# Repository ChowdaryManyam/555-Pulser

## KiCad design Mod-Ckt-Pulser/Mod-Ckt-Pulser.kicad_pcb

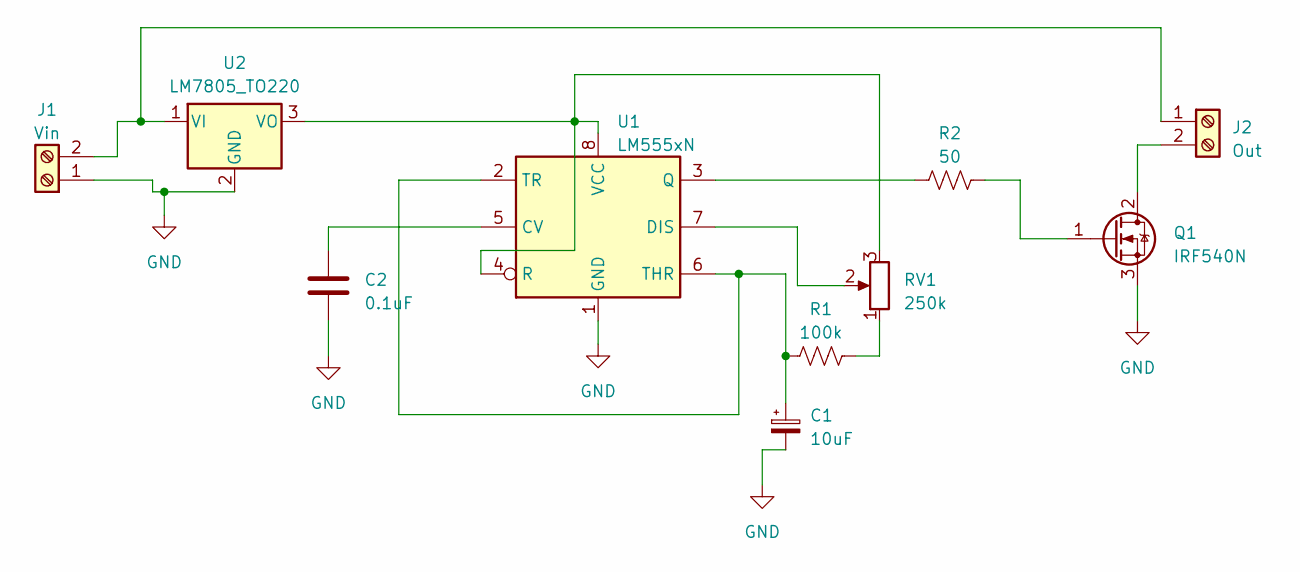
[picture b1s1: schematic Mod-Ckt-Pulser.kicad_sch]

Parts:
C1: 10uF; CP_Radial_D5.0mm_P2.00mm
C2: 0.1uF; C_Disc_D3.0mm_W2.0mm_P2.50mm
J1: Vin; TerminalBlock_Phoenix_MKDS-1,5-2-5.08_1x02_P5.08mm_Horizont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
J2: Out; TerminalBlock_Phoenix_MKDS-1,5-2-5.08_1x02_P5.08mm_Horizont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
Q1: IRF540N; TO-220-3_Vertical
R1: 100k; R_Axial_DIN0204_L3.6mm_D1.6mm_P5.08mm_Horizontal
R2: 50; R_Axial_DIN0204_L3.6mm_D1.6mm_P5.08mm_Horizontal
RV1: 250k; Potentiometer_ACP_CA9-H5_Horizontal
U1: LM555xN; DIP-8_W7.62mm
U2: LM7805_TO220; TO-220-3_Vertical

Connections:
GND: C1.2, C2.2, J1.1, Q1.3 (S), U1.1 (GND), U2.2 (GND)
unnamed: J1.2, J2.1, U2.1 (VI)
unnamed: J2.2, Q1.2 (D)
unnamed: Q1.1 (G), R2.2
unnamed: R1.2, RV1.1
unnamed: C2.1, U1.5 (CV)
unnamed: RV1.2, U1.7 (DIS)
unnamed: R2.1, U1.3 (Q)
unnamed: RV1.3, U1.4 (R), U1.8 (VCC), U2.3 (VO)
unnamed: C1.1, R1.1, U1.2 (TR), U1.6 (THR)

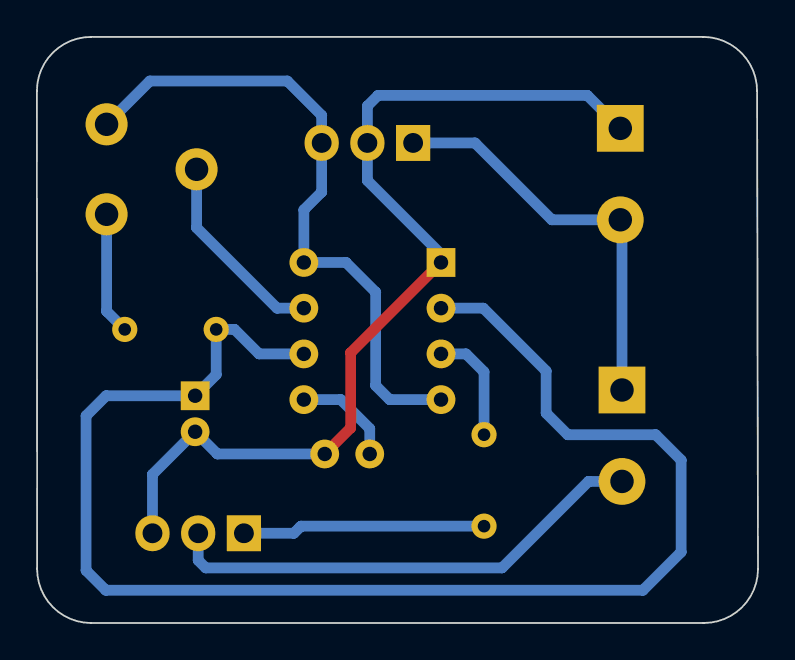
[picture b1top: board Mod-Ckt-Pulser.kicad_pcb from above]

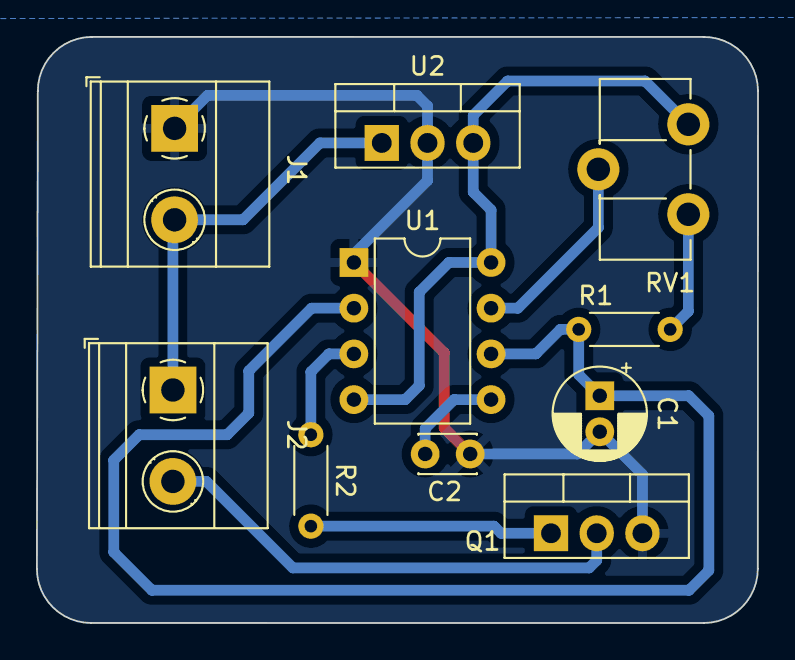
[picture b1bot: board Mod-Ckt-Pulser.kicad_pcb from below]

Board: 2 copper layers, 40.1 x 32.6 mm, 10 parts (10 on the bottom side), 10 nets.
